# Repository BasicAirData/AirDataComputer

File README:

BasicAirData (c) 2014 JLJ

THE PROJECT:

BasicAirData is devoted to Open and free DIY air data instrumentation and telemetry. You can find instruments construction plans and software on the main site.

Right now an Air Data Computer design project is starting; Open source Hardware and Open Source software.

The activity is based on the brand new forum 

http://basicairdata.freeforums.org

Every feedback and feature proposal is welcome

JLJ

CURRENT MEMBERS :

http://www.basicairdata.eu/about.html

ON LINE REFERENCES :

Main site
http://www.basicairdata.eu

Forum
http://basicairdata.freeforums.org/index.php

Facebook page

https://www.facebook.com/BasicAirData

This is a branch!

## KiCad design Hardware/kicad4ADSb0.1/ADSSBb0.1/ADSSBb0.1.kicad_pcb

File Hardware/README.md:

# Hardware Folder
"Release" folder is the work in progress release

In "Asgard" folder you find all the Amaranth i2 ADC related material
* Enclosure	
* Kicad Asgard	Printed Circuit Board
* Pinout	
* Schematic
In "3D support" folder you find free 3D models of the Teensy board 3.5/3.6C

In "Amaranthi2" folder you find all the Amaranth i2 ADC related material
* Enclosure	
* Kicad Amaranth i2	Printed Circuit Board
* Pinout	
* Schematic

In "3D support" folder you find free 3D models of the Teensy board 3.1/3.2, the SD card holder used for the virtual assembly of Amaranth i2 ADC, and 3.5/3.6 Teensy boards.

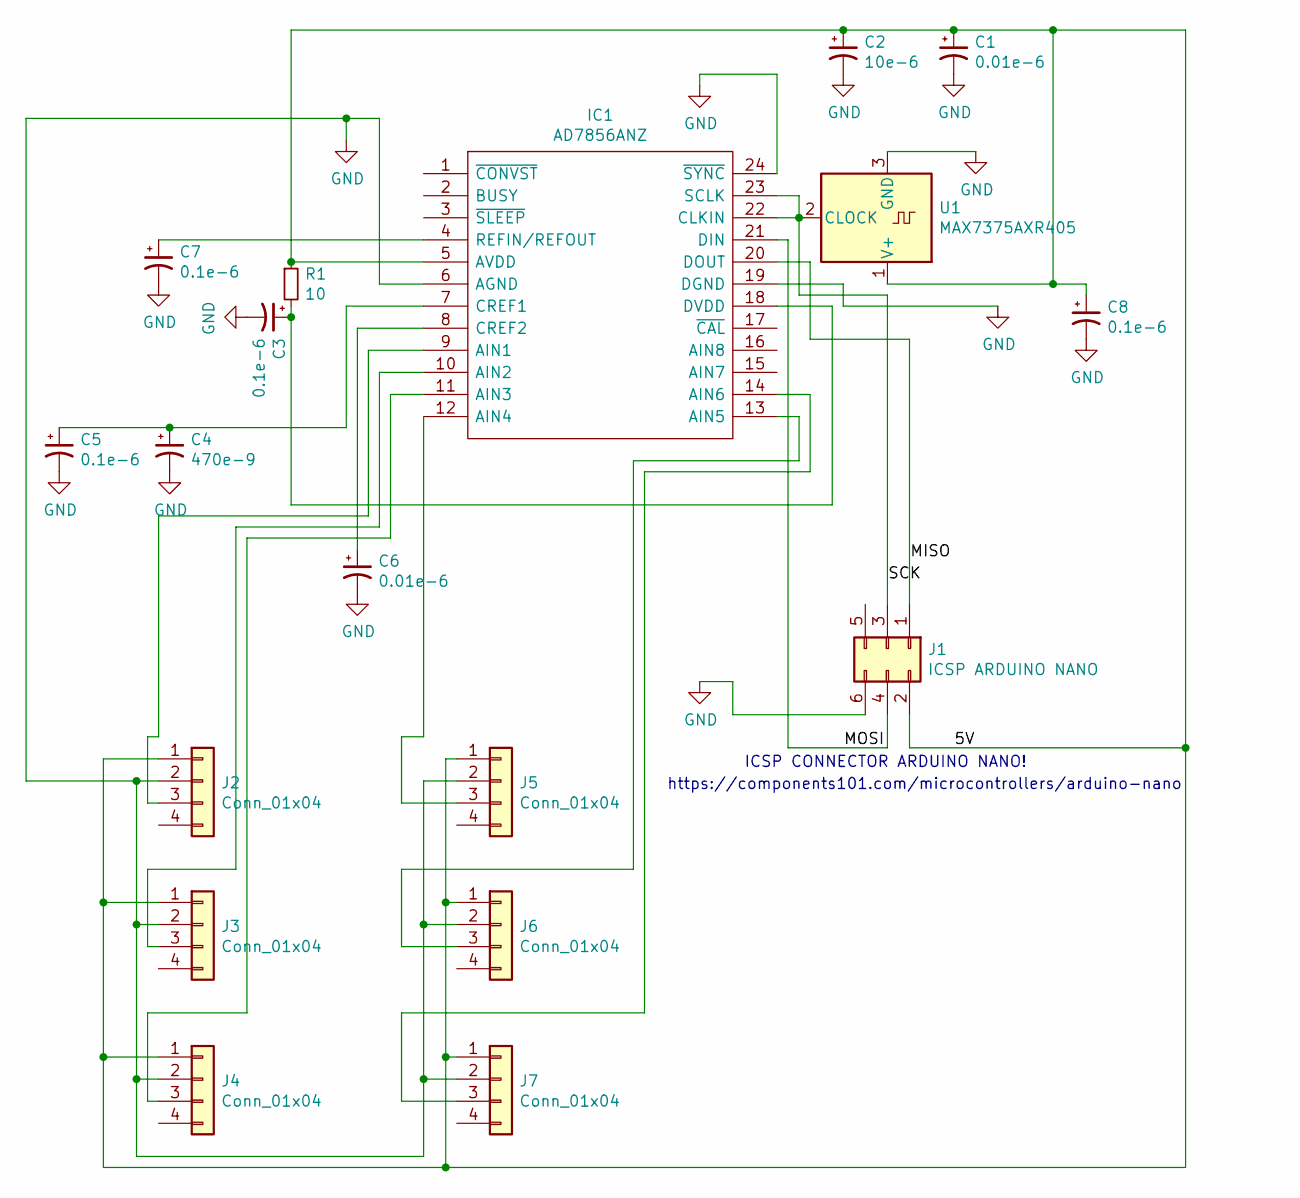
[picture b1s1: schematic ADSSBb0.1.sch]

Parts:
C1, C6: 0.01e-6; CP_Radial_D4.0mm_P1.50mm
C2: 10e-6; CP_Radial_D4.0mm_P1.50mm
C3, C5, C7, C8: 0.1e-6; CP_Radial_D4.0mm_P1.50mm
C4: 470e-9; CP_Radial_D4.0mm_P1.50mm
IC1: AD7856ANZ; DIP-24_W10.16mm; Mouser Part Number 584-AD7856ANZ
J1: ICSP ARDUINO NANO; PinSocket_2x03_P2.54mm_Vertical
J2, J3, J4, J5, J6, J7: Conn_01x04; PinSocket_1x04_P2.54mm_Vertical
R1: 10; R_Axial_DIN0204_L3.6mm_D1.6mm_P1.90mm_Vertical
U1: MAX7375AXR405; SOT-323_SC-70

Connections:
/5V: C1.1, C2.1, C8.1, IC1.5 (AVDD), J1.2, J2.1, J3.1, J4.1, J5.1, J6.1, J7.1, R1.1, U1.1 (V+)
/MISO: IC1.20 (DOUT), J1.1
/MOSI: IC1.21 (DIN), J1.4
/SCK: IC1.22 (CLKIN), IC1.23 (SCLK), J1.3, U1.2 (CLOCK)
GND: C1.2, C2.2, C3.2, C4.2, C5.2, C6.2, C7.2, C8.2, IC1.6 (AGND), IC1.19 (DGND), IC1.24 (~SYNC), J1.6, J2.2, J3.2, J4.2, J5.2, J6.2, J7.2, U1.3 (GND)
unnamed: C3.1, IC1.18 (DVDD), R1.2
unnamed: C4.1, C5.1, IC1.7 (CREF1)
unnamed: C6.1, IC1.8 (CREF2)
unnamed: C7.1, IC1.4 (REFIN/REFOUT)
unnamed: IC1.9 (AIN1), J2.3
unnamed: IC1.10 (AIN2), J3.3
unnamed: IC1.11 (AIN3), J4.3
unnamed: IC1.12 (AIN4), J5.3
unnamed: IC1.13 (AIN5), J6.3
unnamed: IC1.14 (AIN6), J7.3

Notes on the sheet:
https://components101.com/microcontrollers/arduino-nano
ICSP CONNECTOR ARDUINO NANO!

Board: 2 copper layers, 18 parts (3 on the bottom side), 15 nets, no tracks yet.

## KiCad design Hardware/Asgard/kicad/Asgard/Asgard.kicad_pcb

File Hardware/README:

BasicAirData Team

The reference page for the project
http://www.basicairdata.eu/projects/airdatacomputer/

THE PROJECT:

BasicAirData is devoted to Open and free DIY air data instrumentation and telemetry. You can find instruments construction plans and software on the main site.

Right now an Air Data Computer design project is starting; Open source Hardware and Open Source software.

Every feedback and feature proposal is welcome

Basic Air Data Team

Join :

http://www.basicairdata.eu/join

ON LINE REFERENCES :

Main site + Socials
http://www.basicairdata.eu

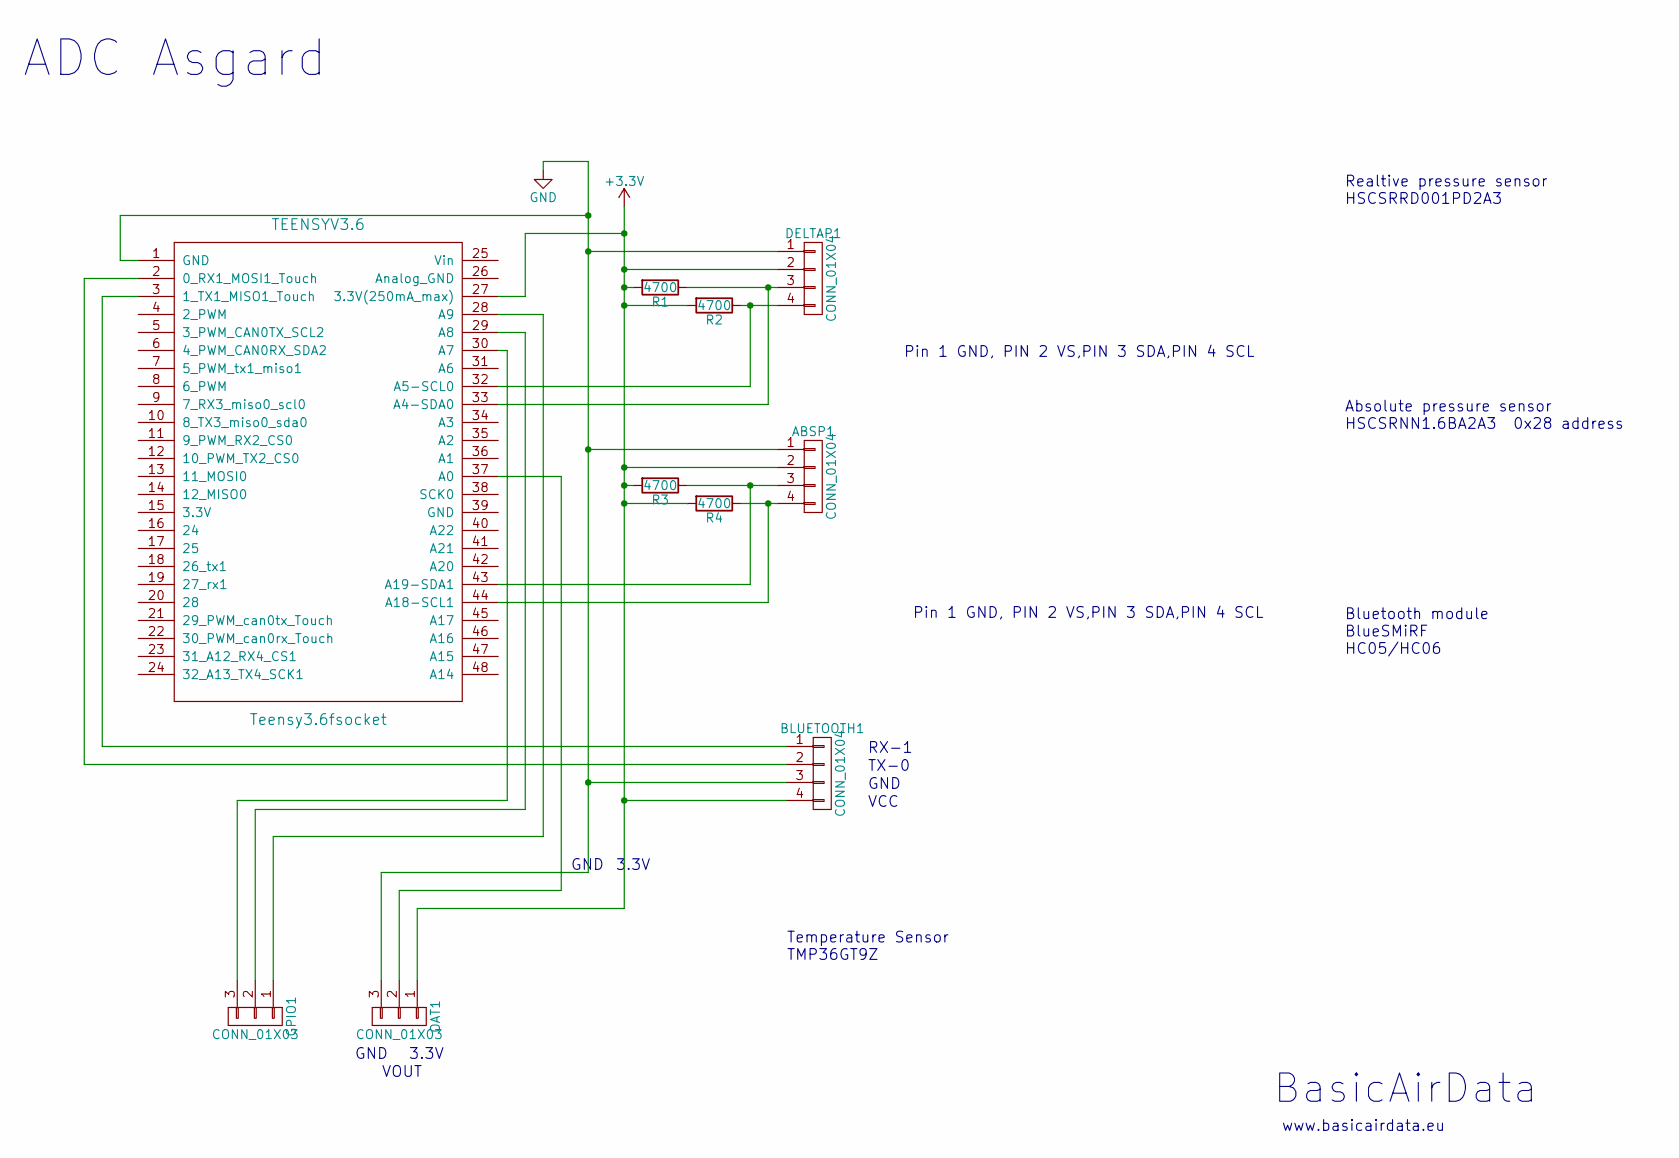
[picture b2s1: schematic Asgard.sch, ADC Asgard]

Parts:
ABSP1: CONN_01X04; Socket_Strip_Straight_1x04_Pitch2.54mm
BLUETOOTH1: CONN_01X04; Socket_Strip_Straight_1x04_Pitch2.54mm
DELTAP1: CONN_01X04; Socket_Strip_Straight_1x04_Pitch2.54mm
GPIO1: CONN_01X03; PINHEAD1-3
OAT1: CONN_01X03; PINHEAD1-3
R1, R2, R3, R4: 4700; R_Axial_DIN0204_L3.6mm_D1.6mm_P1.90mm_Vertical
TEENSYV3.6: Teensy3.6fsocket; Socket_Strip_Teensy3.6_2x24_Pitch2.54mm

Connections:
+3V3: ABSP1.2, BLUETOOTH1.4, DELTAP1.2, OAT1.1, R1.2, R2.2, R3.2, R4.2, TEENSYV3.6.27 (3.3V(250mA_max))
GND: ABSP1.1, BLUETOOTH1.3, DELTAP1.1, OAT1.3, TEENSYV3.6.1 (GND)
unnamed: ABSP1.3, R3.1, TEENSYV3.6.43 (A19-SDA1)
unnamed: ABSP1.4, R4.1, TEENSYV3.6.44 (A18-SCL1)
unnamed: BLUETOOTH1.1, TEENSYV3.6.3 (1_TX1_MISO1_Touch)
unnamed: BLUETOOTH1.2, TEENSYV3.6.2 (0_RX1_MOSI1_Touch)
unnamed: DELTAP1.3, R1.1, TEENSYV3.6.33 (A4-SDA0)
unnamed: DELTAP1.4, R2.1, TEENSYV3.6.32 (A5-SCL0)
unnamed: GPIO1.1, TEENSYV3.6.28 (A9)
unnamed: GPIO1.2, TEENSYV3.6.29 (A8)
unnamed: GPIO1.3, TEENSYV3.6.30 (A7)
unnamed: OAT1.2, TEENSYV3.6.37 (A0)

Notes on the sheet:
BasicAirData
RX-1
TX-0
GND
VCC
Absolute pressure sensor HSCSRNN1.6BA2A3 0x28 address
Realtive pressure sensor HSCSRRD001PD2A3
Bluetooth module BlueSMiRF HC05/HC06
Pin 1 GND, PIN 2 VS,PIN 3 SDA,PIN 4 SCL
ADC Asgard
www.basicairdata.eu
Temperature Sensor TMP36GT9Z
3.3V
VOUT

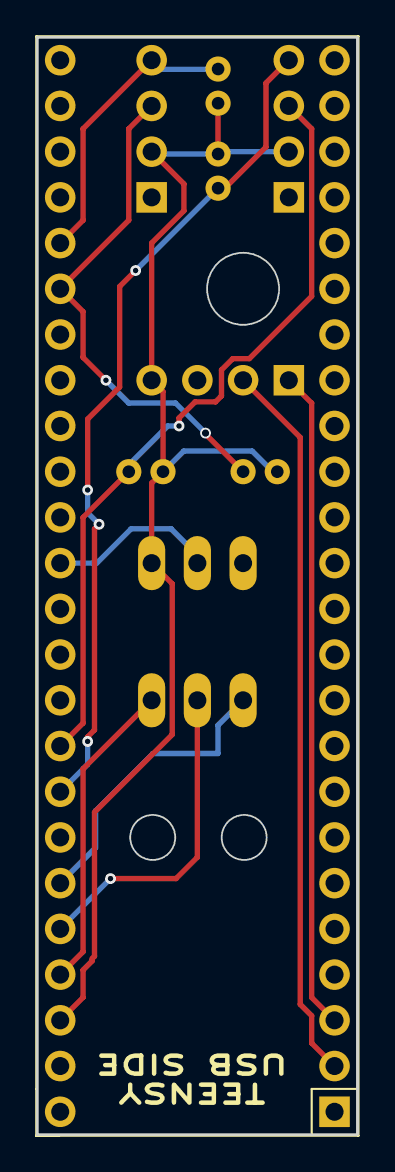
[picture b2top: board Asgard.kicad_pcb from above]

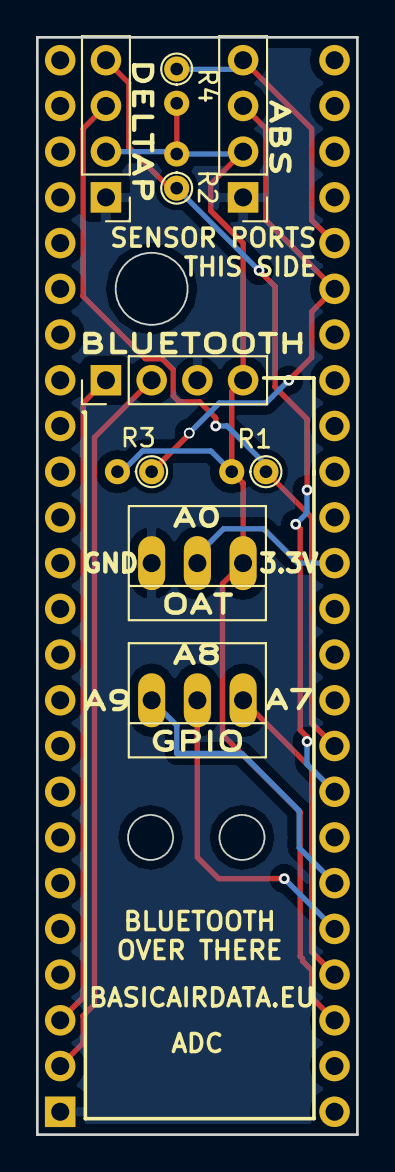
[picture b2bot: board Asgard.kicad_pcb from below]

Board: 2 copper layers, 17.8 x 61.0 mm, 10 parts (9 on the bottom side), 12 nets.

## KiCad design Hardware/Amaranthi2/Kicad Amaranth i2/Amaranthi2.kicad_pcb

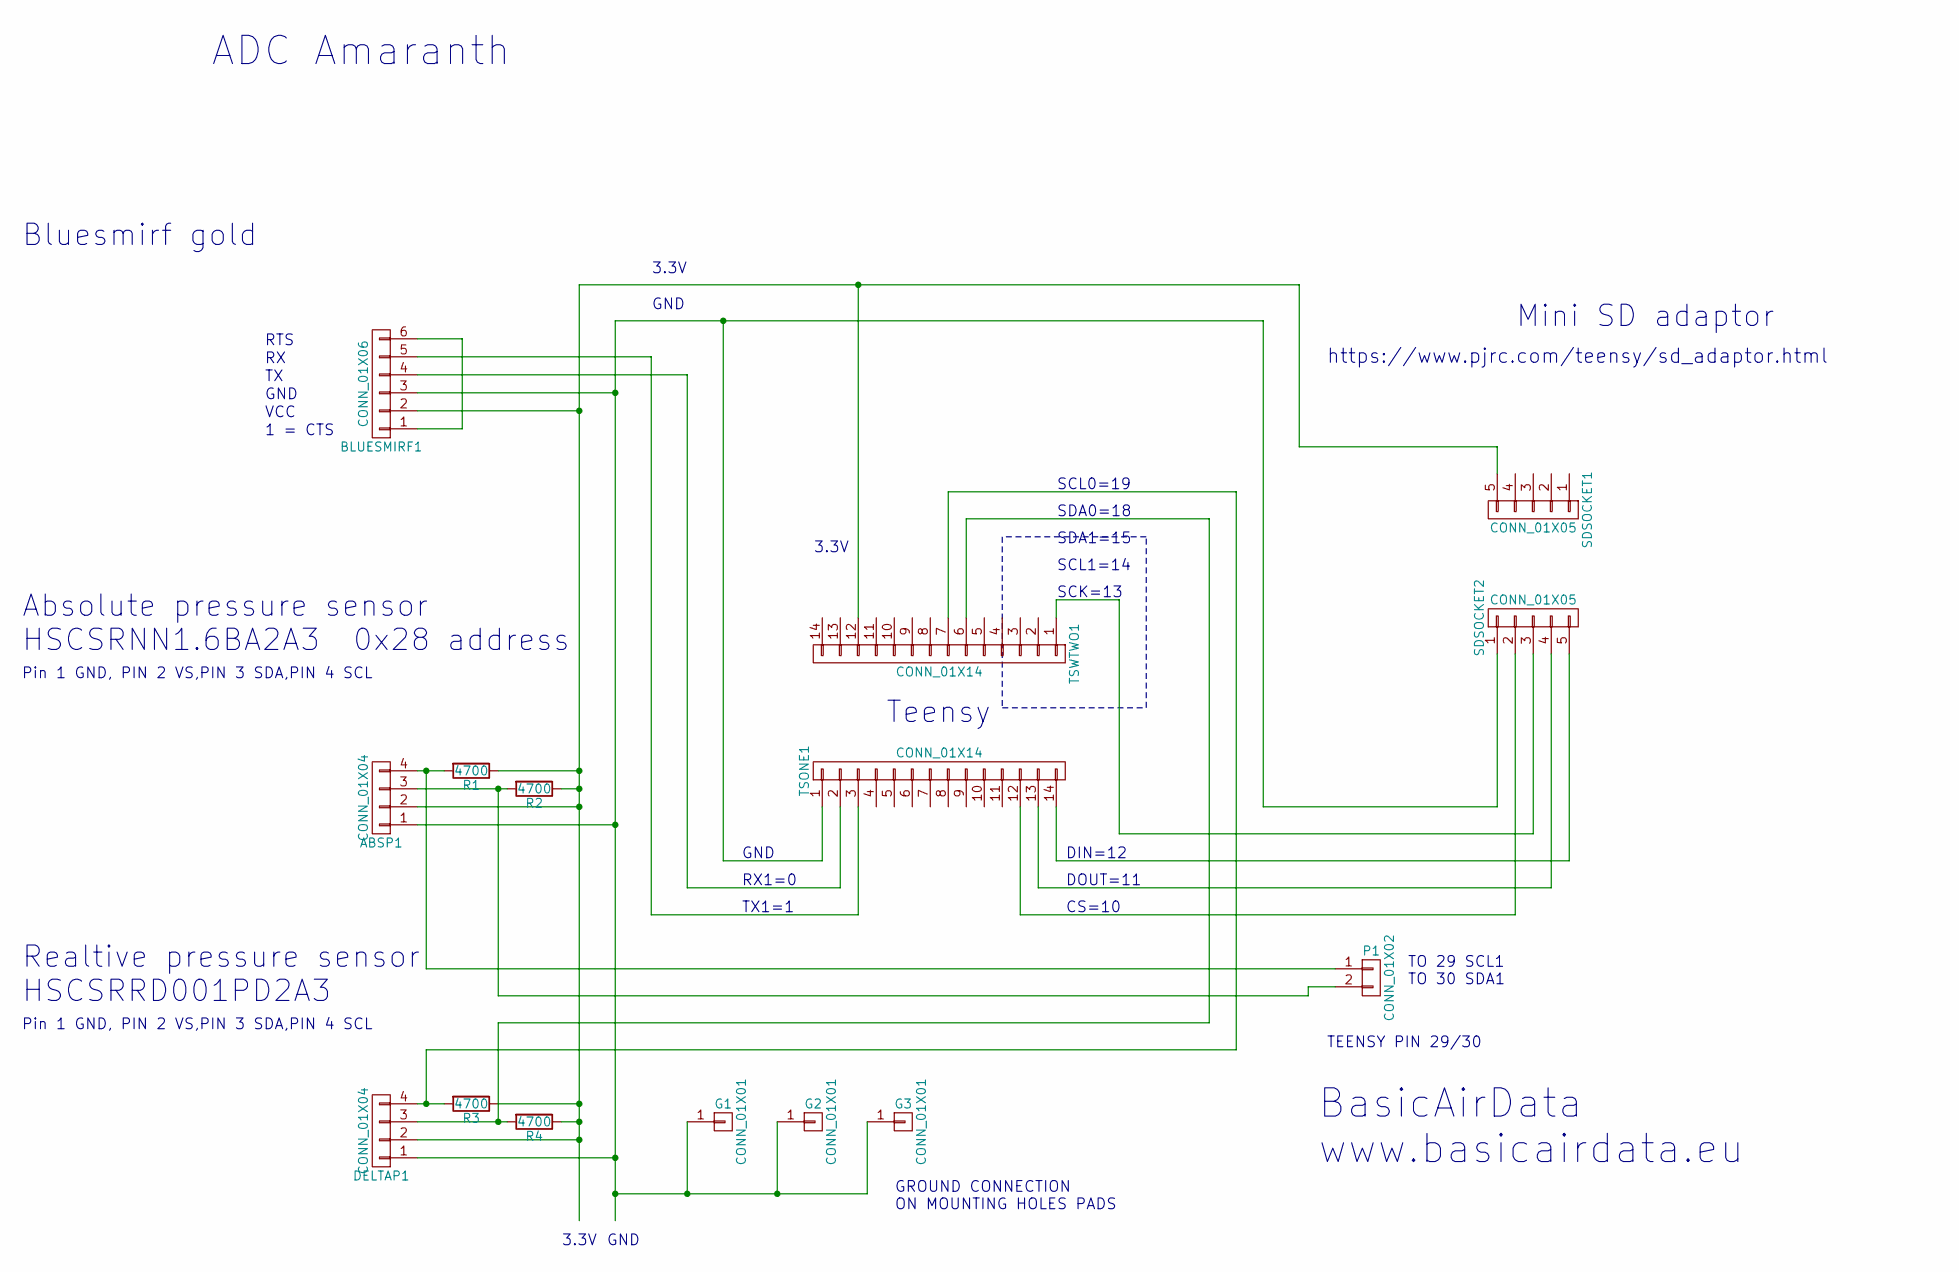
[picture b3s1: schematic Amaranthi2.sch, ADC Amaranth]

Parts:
ABSP1: CONN_01X04; Socket_Strip_Angled_1x04
BLUESMIRF1: CONN_01X06; Socket_Strip_Straight_1x06
DELTAP1: CONN_01X04; Socket_Strip_Angled_1x04
G1, G2, G3: CONN_01X01; Pin_Header_Straight_1x01
P1: CONN_01X02; Socket_Strip_Angled_1x02
R1, R2, R3, R4: 4700; R_1206
SDSOCKET1, SDSOCKET2: CONN_01X05; Socket_Strip_Straight_1x05
TSONE1: CONN_01X14; Socket_Strip_Straight_1x14
TSWTWO1: CONN_01X14; Socket_Strip_Straight_1x14

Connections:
unnamed: ABSP1.1, BLUESMIRF1.3, DELTAP1.1, G1.1, G2.1, G3.1, SDSOCKET2.1, TSONE1.1
unnamed: ABSP1.2, BLUESMIRF1.2, DELTAP1.2, R1.1, R2.1, R3.1, R4.1, SDSOCKET1.5, TSWTWO1.12
unnamed: ABSP1.3, P1.2, R2.2
unnamed: ABSP1.4, P1.1, R1.2
unnamed: BLUESMIRF1.1, BLUESMIRF1.6
unnamed: BLUESMIRF1.4, TSONE1.2
unnamed: BLUESMIRF1.5, TSONE1.3
unnamed: DELTAP1.3, R4.2, TSWTWO1.6
unnamed: DELTAP1.4, R3.2, TSWTWO1.7
unnamed: SDSOCKET2.2, TSONE1.12
unnamed: SDSOCKET2.3, TSWTWO1.1
unnamed: SDSOCKET2.4, TSONE1.13
unnamed: SDSOCKET2.5, TSONE1.14

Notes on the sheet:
ADC Amaranth
BasicAirData www.basicairdata.eu
Mini SD adaptor
Bluesmirf gold
Absolute pressure sensor HSCSRNN1.6BA2A3 0x28 address
Realtive pressure sensor HSCSRRD001PD2A3
https://www.pjrc.com/teensy/sd_adaptor.html
1 = CTS
Pin 1 GND, PIN 2 VS,PIN 3 SDA,PIN 4 SCL
GND
SCK=13
Teensy
RX1=0
TX1=1
SCL0=19
SDA0=18
SDA1=15
CS=10
DIN=12
DOUT=11
3.3V
GROUND CONNECTION ON MOUNTING HOLES PADS
VCC
RTS
TEENSY PIN 29/30
TO 29 SCL1 TO 30 SDA1
SCL1=14

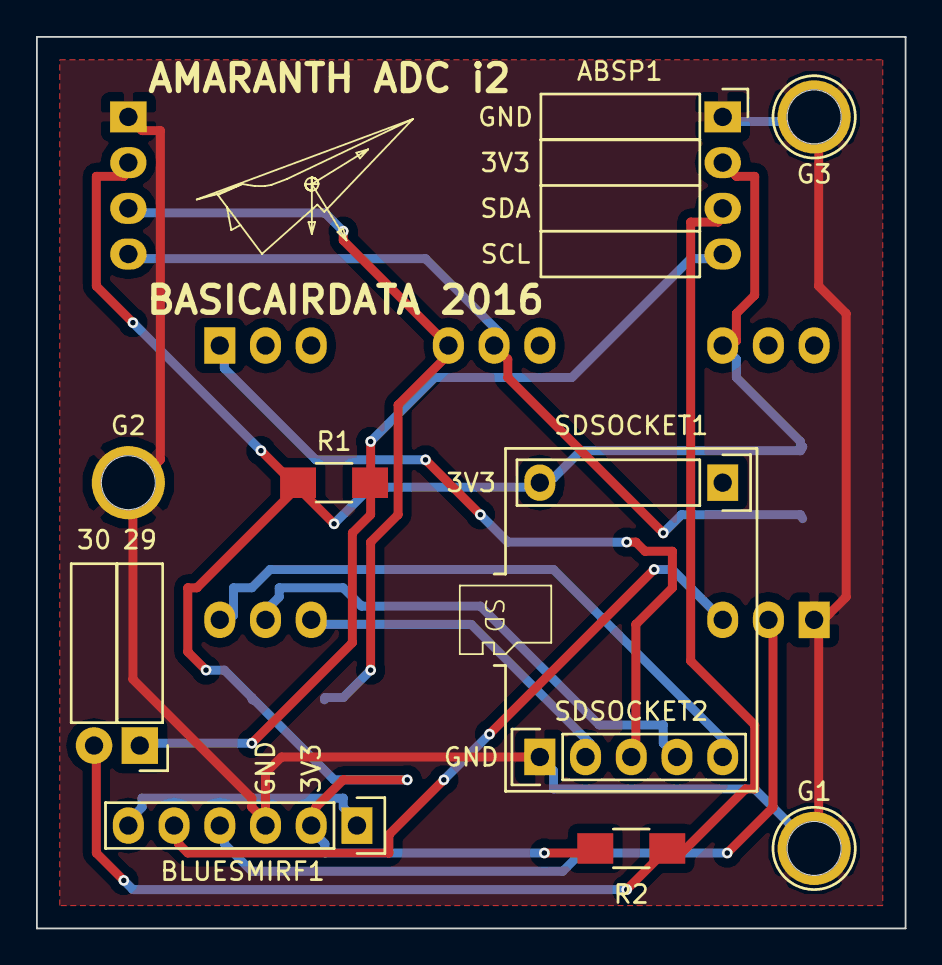
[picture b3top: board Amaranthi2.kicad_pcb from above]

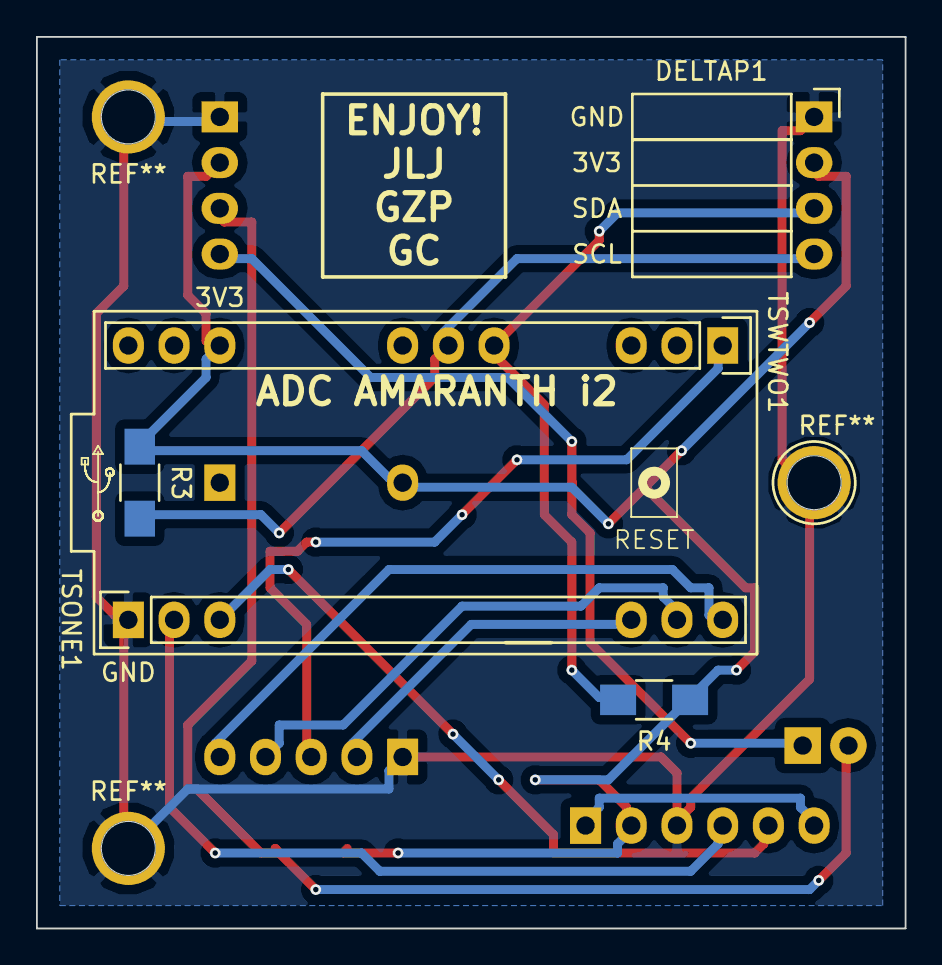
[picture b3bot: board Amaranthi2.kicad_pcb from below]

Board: 2 copper layers, 48.3 x 49.5 mm, 15 parts (6 on the bottom side), 13 nets.

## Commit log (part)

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2017-03-12 Added Send Air Data.jpg
2017-03-12 Added AC1.xml
2017-03-12 Added AC1.jpg
2017-03-12 Added UC1.jpg
2017-03-13 Added Store Data.xml
2017-03-13 Added Store Data.jpg
2017-03-13 Added Receive Data Periodically.xml
2017-03-13 Added Receive Data Periodically.jpg
2017-03-13 Added Use Case Configuration.jpg
2017-03-13 Added Use Case Configuration.xml
2017-03-13 Added Compute Air Data.xml
2017-03-13 Added Compute Air Data.jpg
2017-03-13 Added Configuration.xml
2017-03-13 Added Configuration.jpg
2017-03-13 Added Send Air Data.xml
2017-03-13 Added Acquire Sensors Data.xml
2017-03-13 Added Acquire Sensors Data.jpg
2017-03-13 Redo comments
2017-03-13 AirDC
2017-03-14 Up Lib Zip
2017-03-14 Remove compile test code
2017-03-16 Doc updated
2017-03-16 Altitude fix
2017-03-16 up ADC Doc
2017-03-16 reorder
2017-03-16 Up docu
2017-03-19 ADC Communication Updated
2017-03-21 Some doc
2017-03-22 Opened Asgard
2017-03-22 struc
2017-03-22 Added Architecture.xml
2017-03-22 Added Architecture.png
2017-03-22 Diagramas
2017-03-25 Up 3D Teensy 3.6
2017-03-27 template Kicad
2017-03-27 Update initial file for Kicad with template
2017-03-27 Updated Template Kicad
2017-03-27 template
2017-03-27 Initial setup of Kicad
    Libraries setup
2017-03-28 Proposal Asgard Schematics
    Ready for routing
2017-03-28 PCB Preliminary Layout
2017-03-28 PCB-Init Commit
2017-03-29 Libs Kicad
2017-03-31 STEP Teensyv3.6
2017-04-02 step3D
2017-04-05 c factor
2017-04-05 c figure
2017-04-05 c curve png
2017-04-05 up range
2017-04-10 updoc
2017-04-10 Created HW doc folder
2017-04-10 Added Costi.html
2017-04-10 Added Costi.png
2017-04-16 Added Temperature sensor Test01
2017-04-17 Abs sensor test
2017-04-17 FW for test
2017-04-17 Changed A9 to A0 for the Temperature sensor
2017-04-17 Hw test code completed
2017-04-18 HW test sketch for Asgard ADC
2017-04-18 serial1
2017-04-18 secret is the wash
2017-04-18 Test added
2017-04-18 Tree
2017-04-18 Test Code
    New SSC lib is starting to beat!
2017-04-19 ADC Algorithm
    Starting to pull together the code
2017-04-19 Test Sketch Finished
2017-04-19 Some line
2017-04-19 Firmware draft
2017-04-19 CheckReadings
2017-04-19 ADC Alive
2017-04-19 SDSave
2017-04-20 Lay comm skeleton
2017-04-20 SD Operational
2017-04-20 50Hz
2017-04-21 AirDC+
2017-04-21 CapCom basics
2017-04-23 Communication Stuff and code
2017-04-24 renewcom
2017-04-24 Working Comm Interface
2017-04-24 Comm up to msg#7
2017-04-25 Added msg #17 #18
2017-04-25 doccomm
2017-04-26 Comm msg #10 exp
2017-04-26 Alive and kiking
    AsgardADC0.1 intial full run ok
    Update Common Message Base with implementation status
2017-04-26 Created Android Folder
2017-04-26 Work in progress with interrupt timing online
2017-04-27 Time interval on test
2017-04-27 #DFS,50
2017-04-28 reorde
2017-04-28 Fixed Temp in SI units, K
2017-04-28 Removed #define cloud
2017-04-28 Sorting
    Sorting
    Serial Test Session
    Grouped Teensy Libraries
2017-04-28 Test Serial
    Fixed release no
2017-04-29 Deg K
2017-04-29 Removed double '\n?
    \n is now appended only in the main sketch by the .println command.
2017-05-04 Add ADCTester
2017-05-07 Attach BroadcastReceiver on Create
2017-05-07 Add status messages to terminal output
2017-05-08 BT ON
2017-05-08 Update the terminal in UI Thread
2017-05-08 bton
2017-05-08 Serial test
    Command line Linux Fedora
2017-05-09 testbuffer
2017-05-09 delta
2017-05-09 BT
    BT modules interface ok. ADCTester Android app seems to work fine on my
    phone :-)
2017-05-09 Delta Firmware
2017-05-11 SD Management messages Added
    Updated ADCCMS
2017-05-12 Started to implement file manager functions
2017-05-12 Msg #17 wip
2017-05-12 Included SD handling routines
    Untested release
2017-05-13 Msg 17 1+2
    ok!
2017-05-13 msg 17
    3 ok
2017-05-13 msg 17
    4 ok
2017-05-14 Msg 11 + 12 +13
    Tested, updated doc
2017-05-14 Zip purged
2017-05-14 HC-05
    The test with HC-05 board started
2017-05-22 Updated Schematics
    Addedd indication for HC-05/HC-06 Compatibility
2017-05-22 Fiddling with packages
2017-05-22 Added doc
    Schematics pdf
    New PCB laysout started
2017-05-23 Schematics update
    GPIO connector is hard to place
2017-05-23 PCB Rel 1
    First Release of PCB
2017-05-24 PCB proposal
2017-05-24 PCB Candidate
    Vertical mounted resistors
2017-05-24 PCB Candidate 2
2017-05-24 PCB Candidate 3
2017-05-24 PCB candidate 4
2017-05-25 PCB Candidate 5
    Added labels on silkboard
2017-05-25 PCB Candidate 6
2017-05-25 3D model
2017-05-25 Holes updated
2017-05-25 Corrected rounded sizes
2017-05-26 Updated Holes
2017-05-27 Limit the number of terminal lines
2017-05-28 Moved holes in PCB
2017-05-28 Pressure sensors inverted
2017-05-28 Updated 3D model
    Holes moved
2017-05-30 Polishing the board
2017-05-30 Getting files ready for PCB
2017-06-03 3D Print files
    STL Files for 3D print of Asgard Enclosure
2017-07-17 ru
    commented lines
2017-09-28 rdme
2017-10-25 BOM Kicad
2017-10-25 BOM 2
2017-10-26 WIN PCB files
2017-11-06 fixdoc
2017-11-14 Arduino.h
2017-11-27 Specs.xml
2018-01-04 Add enclosure drawings
2018-01-07 Implementation of communication protocol v0.4 + independent freqs
2018-01-07 Set the acquisition frequency depending on the 3 required data frequencies
2018-01-07 Fine tuning of acquisition frequency
2018-01-08 Added current release folder
    The number of ADC release is now standardized and equal to 0.0.0
2018-01-08 Tune the loop delay=5% of the minimum of the log delays
2018-01-09 Rup Scprit
    Init Scilab Scripts
2018-01-09 Fix the interval of first sample
2018-01-10 Rup Scilab
2018-01-10 Viscosity Pas
    Viscosity Pas , 8 decimal digits required
2018-01-10 Reversed qc
    qc was not of the right sign. Following the assembly intructions the
    resulting qc sign should be correct
2018-01-10 IAS ok
2018-01-10 Add the ability to abort a file dump
2018-01-11 Closes #58 - Set the default data frequencies to zero
2018-01-11 Closes #59 - Return 8 decimals for Air Viscosity
2018-01-12 Scialb function to calculate moist air heat ratio added
    Scialb function to calculate moist air heat ratio added
2018-01-12 Prunned no longer used code in AirDC
    Prunned no longer used functions in AirDC
2018-01-13 Implementation of message
2018-01-13 Finish structure for implementation of DTS message
2018-01-13 Eliminated obsolete Readme.md
    Eliminated obsolete Readme.md
2018-01-14 Closes #56 - New method to check if the SD is present
2018-01-14 fix the SD init when mounted
2018-01-14 Readme updated
    Readme updated
2018-01-14 Change the LEAVE_AS_IS character to =
2018-01-14 Closes #65 - Load the CONFIG.CFG file on the SDCard on start
2018-01-15 Added msg 19 e 20 for #62 . Added cpcv calculation script
    Added msg 19 e 20 for #62 . Added cpcv Scilab calculation script
2018-01-16 Deltap zeroing data test in Scilab
    Deltap zeroing data test in Scilab
2018-01-16 Added GPS Logger track support to SCilab script
    Added GPS Logger track support to SCilab script
2018-01-16 Fix a possible loss of message when 2 messages are queued in the buffer
2018-01-16 A couple of general improvements and cleanups
2018-01-17 Added Figure to Scilab Scripts
    Added Figure to Scilab Scripts
2018-01-17 Closed #71
    Unc
2018-01-17 Arduino IDE folder
2018-01-17 Close #60
    Added uncertainty expression
2018-01-17 Del ODT temp
    Del ODT temp
2018-01-17 Closed #73
    if selected into Scilab file (writetoQGISfile=1) a QGIS usable file is
    produced from ADC + GPS Data
2018-01-17 Syntax Fixed
    Syntax Fixed
2018-01-18 Added QGIS Image
    Added QGIS Image
2018-01-18 Addef PNG to Script Output
    Addef PNG to Script Output
2018-01-18 UPDATE IMAGES
2018-01-18 Closes #79 - Assign the right timestamp to the files on SD
2018-01-18 Use a new progressive number using the ? character in the filename
2018-01-19 Temp 19 20
2018-01-19 .ino small mod
2018-01-20 Added Basic Message No 19 and No 20 implementation
    Added Basic Message No 19 and No 20 implementation
2018-01-20 Markup Common Message Set
    Markup Common Message Set
2018-01-22 Completed Msg No.19 and No.20
    Completed Msg No.19 and No.20. No 19 message command EXE Mode 2
    implementation will be completed in a second stage
2018-01-22 Complete No.19 and No.,20 #1
    Completed Msg No.19 and No.20. No 19 message command EXE Mode 2
    implementation will be completed in a second stage
2018-01-23 Allow to delete the current active file if ADC is not recording
2018-01-30 Added Hardware paramters for sensors
    Added Hardware paramters for sensors
2018-01-31 Add a comment TODO before compiling
2018-02-02 Closes #88
    Closes #88
2018-02-06 Add files timestamp in the FMA,LST message
2018-02-08 Add file timestamp in the FMA,PRP message
2018-04-16 Added Hex File
2018-04-16 FW update
2018-05-30 Script and data update
2018-06-27 Added Air Data Flow.xml
2018-07-05 Added IssueP.xml
2018-09-21 UPPDF
2019-01-10 BS
    BS
2019-01-10 Docygen
2019-01-10 Doxygen
2019-01-21 playing with kicad
    Kicad draft
2019-01-22 Kicad experiments
    Kicad experiments
2019-01-23 Kicad +
    Kicad +
